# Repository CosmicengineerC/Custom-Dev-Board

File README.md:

# Custom-Dev-Board
A custom dev board designed by me to allow me to create intricate projects

A minimal, high-performance prototyping board based on the Raspberry Pi RP2040.

Core Specs
MCU: Dual ARM Cortex-M0+ (133 MHz, 264 KB SRAM).

Storage: 2 MB QSPI Flash.

I/O: 20-pin breakout (GPIO, ADC, UART, SPI, I2C).

Clock: 12 MHz Crystal.

Power: USB-C (5V) to 3.3V LDO.

## How to Use:
Honestly idk, however you want, its a cheaper version of an esp-32, meant for small projects, its meant to be disposable in the sense of messing it up before a 100 dollar chip.

## Why I made this:

I made this because i wanted to test my skills, and allow me to easily create more intricate projects with ease. It is also a good starter project to learn the intricacies of PCB design.

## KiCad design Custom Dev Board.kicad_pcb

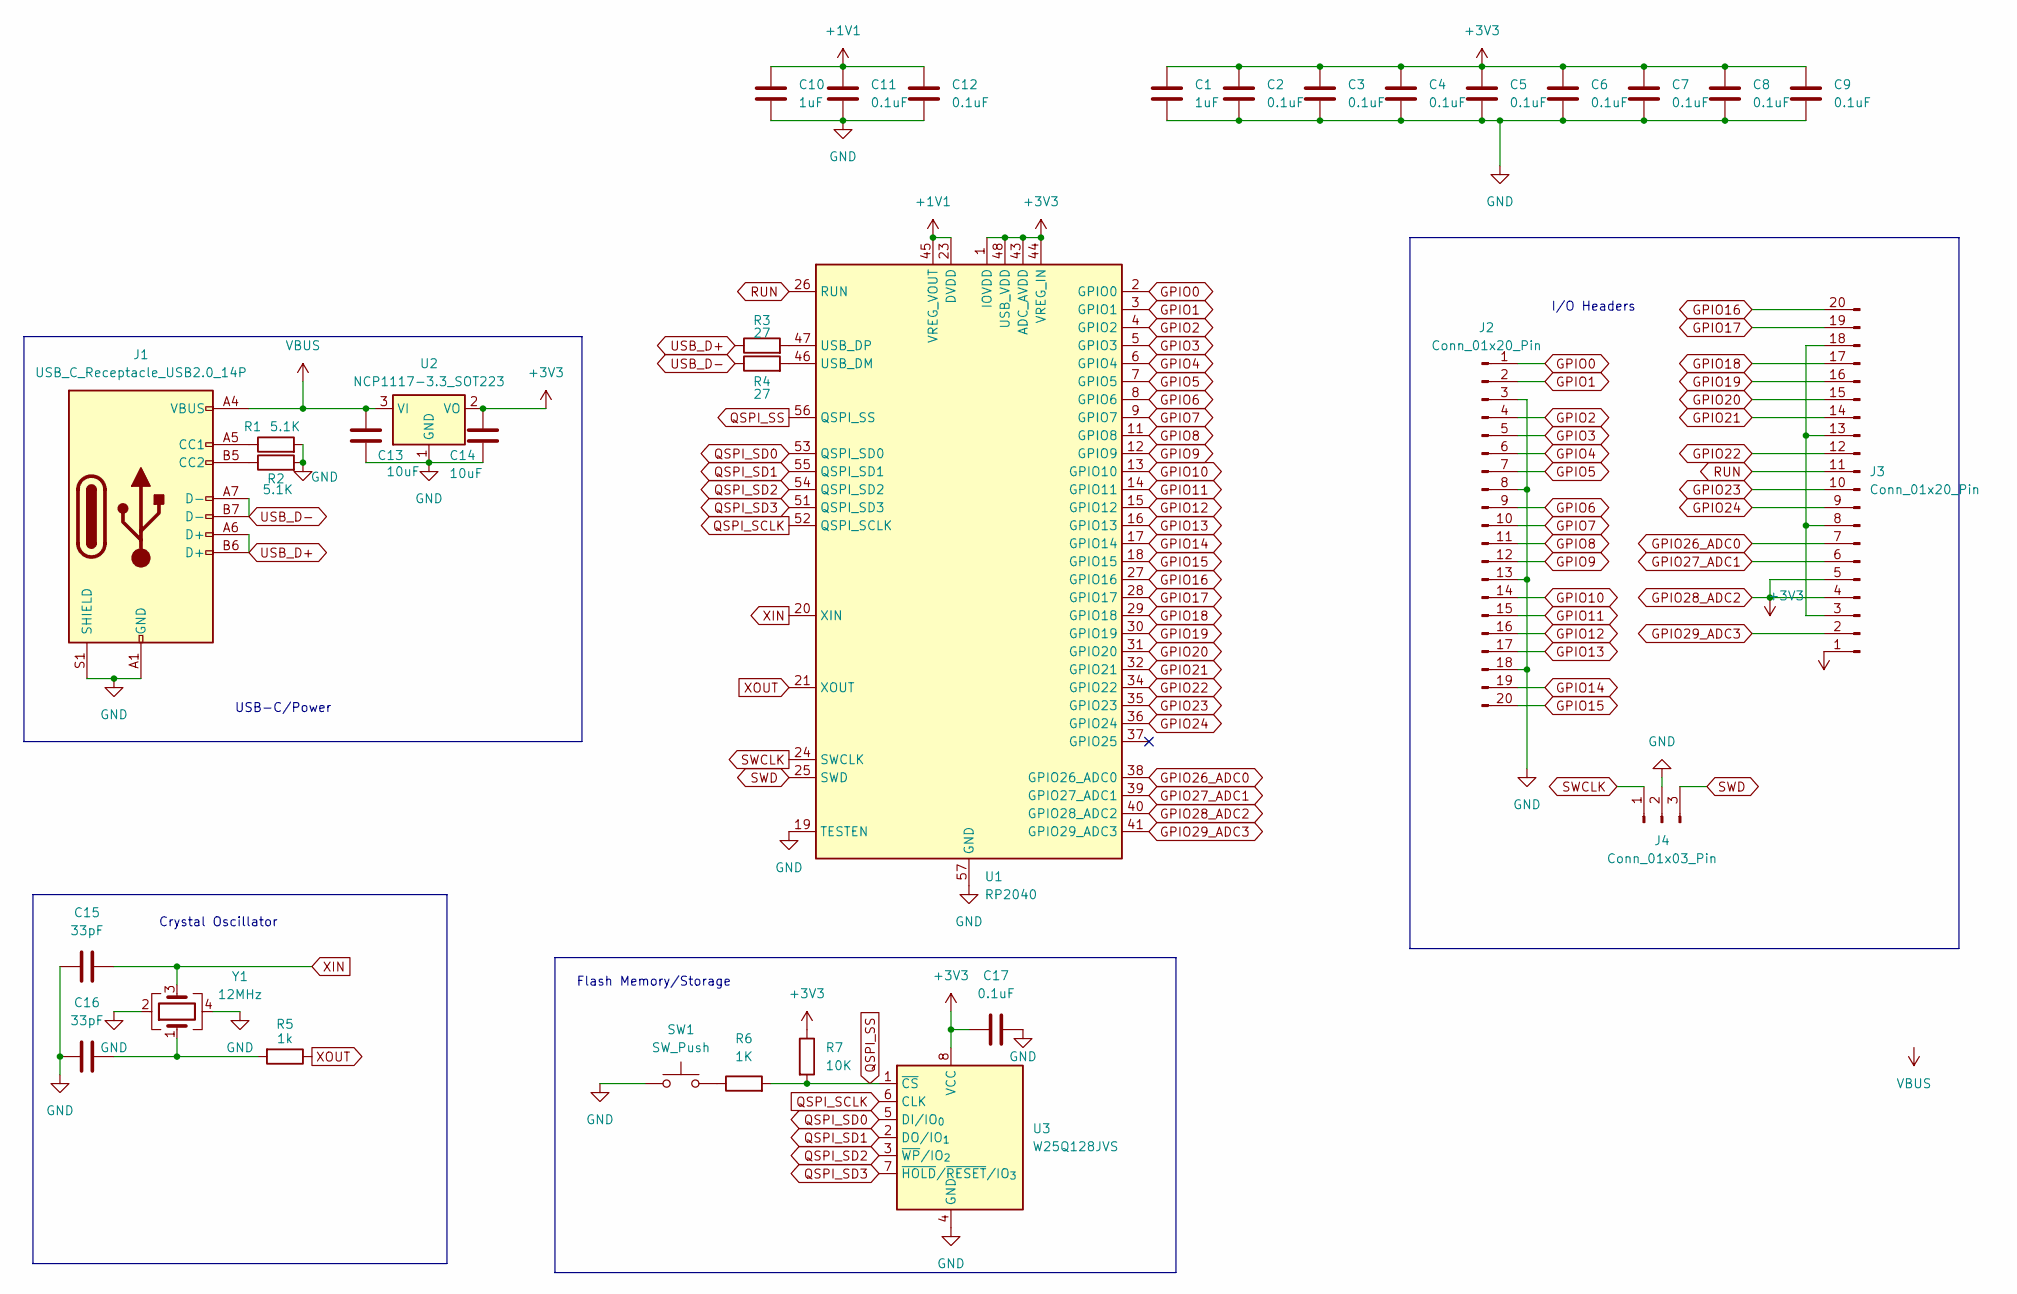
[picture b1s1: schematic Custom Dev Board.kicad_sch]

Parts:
C1, C10: 1uF; C_0402_1005Metric
C2, C3, C4, C5, C6, C7, C8, C9, C11, C12, C17: 0.1uF; C_0402_1005Metric
C13, C14: 10uF; C_0603_1608Metric
C15, C16: 33pF; C_0402_1005Metric
J1: USB_C_Receptacle_USB2.0_14P; USB_C_Receptacle_HRO_TYPE-C-31-M-12
J2, J3: Conn_01x20_Pin; PinHeader_1x20_P2.54mm_Vertical
J4: Conn_01x03_Pin; PinHeader_1x03_P2.54mm_Vertical
R1, R2: 5.1K; R_0402_1005Metric
R3, R4: 27; R_0402_1005Metric
R5: 1k; R_0402_1005Metric
R6: 1K; R_0402_1005Metric
R7: 10K; R_0402_1005Metric
SW1: SW_Push; SW_Push_SPST_NO_Alps_SKRK
U1: RP2040; QFN-56-1EP_7x7mm_P0.4mm_EP3.2x3.2mm
U2: NCP1117-3.3_SOT223; SOT-223-3_TabPin2
U3: W25Q128JVS; SOIC-8_5.3x5.3mm_P1.27mm
Y1: 12MHz; Crystal_SMD_3225-4Pin_3.2x2.5mm

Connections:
+1V1: C10.1, C11.1, C12.1, U1.23 (DVDD), U1.45 (VREG_VOUT), U1.50 (DVDD)
GND: C1.2, C2.2, C3.2, C4.2, C5.2, C6.2, C7.2, C8.2, C9.2, C10.2, C11.2, C12.2, C13.2, C14.2, C15.1, C16.1, C17.1, J1.A1 (GND), J1.A12 (GND), J1.B1 (GND), J1.B12 (GND), J1.S1 (SHIELD), J2.3, J2.8, J2.13, J2.18, J4.2, R1.2, R2.2, SW1.1, U1.19 (TESTEN), U1.57 (GND), U2.1 (GND), U3.4 (GND), Y1.2, Y1.4
GPIO0: J2.1, U1.2 (GPIO0)
GPIO1: J2.2, U1.3 (GPIO1)
GPIO2: J2.4, U1.4 (GPIO2)
GPIO3: J2.5, U1.5 (GPIO3)
GPIO4: J2.6, U1.6 (GPIO4)
GPIO5: J2.7, U1.7 (GPIO5)
GPIO6: J2.9, U1.8 (GPIO6)
GPIO7: J2.10, U1.9 (GPIO7)
GPIO8: J2.11, U1.11 (GPIO8)
GPIO9: J2.12, U1.12 (GPIO9)
GPIO10: J2.14, U1.13 (GPIO10)
GPIO11: J2.15, U1.14 (GPIO11)
GPIO12: J2.16, U1.15 (GPIO12)
GPIO13: J2.17, U1.16 (GPIO13)
GPIO14: J2.19, U1.17 (GPIO14)
GPIO15: J2.20, U1.18 (GPIO15)
GPIO16: J3.20, U1.27 (GPIO16)
GPIO17: J3.19, U1.28 (GPIO17)
GPIO18: J3.17, U1.29 (GPIO18)
GPIO19: J3.16, U1.30 (GPIO19)
GPIO20: J3.15, U1.31 (GPIO20)
GPIO21: J3.14, U1.32 (GPIO21)
GPIO22: J3.12, U1.34 (GPIO22)
GPIO23: J3.10, U1.35 (GPIO23)
GPIO24: J3.9, U1.36 (GPIO24)
GPIO26_ADC0: J3.7, U1.38 (GPIO26_ADC0)
GPIO27_ADC1: J3.6, U1.39 (GPIO27_ADC1)
GPIO28_ADC2: C1.1, C2.1, C3.1, C4.1, C5.1, C6.1, C7.1, C8.1, C9.1, C14.1, C17.2, J3.4, J3.5, R7.1, U1.1 (IOVDD), U1.10 (IOVDD), U1.22 (IOVDD), U1.33 (IOVDD), U1.40 (GPIO28_ADC2), U1.42 (IOVDD), U1.43 (ADC_AVDD), U1.44 (VREG_IN), U1.48 (USB_VDD), U1.49 (IOVDD), U2.2 (VO), U3.8 (VCC)
GPIO29_ADC3: J3.2, U1.41 (GPIO29_ADC3)
unnamed: C16.2, R5.2, Y1.1
unnamed: J1.A5 (CC1), R1.1
unnamed: J1.B5 (CC2), R2.1
unnamed: J3.3, J3.8, J3.13, J3.18
unnamed: R6.1, SW1.2
unnamed: R4.2, U1.46 (USB_DM)
unnamed: R3.2, U1.47 (USB_DP)
QSPI_SCLK: U1.52 (QSPI_SCLK), U3.6 (CLK)
QSPI_SD0: U1.53 (QSPI_SD0), U3.5 (DI/IO_{0})
QSPI_SD1: U1.55 (QSPI_SD1), U3.2 (DO/IO_{1})
QSPI_SD2: U1.54 (QSPI_SD2), U3.3 (~WP/IO_{2})
QSPI_SD3: U1.51 (QSPI_SD3), U3.7 (~HOLD/~RESET/IO_{3})
QSPI_SS: R6.2, R7.2, U1.56 (QSPI_SS), U3.1 (~CS)
RUN: J3.11, U1.26 (RUN)
SWCLK: J4.1, U1.24 (SWCLK)
SWD: J4.3, U1.25 (SWD)
USB_D+: J1.A6 (D+), J1.B6 (D+), R3.1
USB_D-: J1.A7 (D-), J1.B7 (D-), R4.1
VBUS: C13.1, J1.A4 (VBUS), J1.A9 (VBUS), J1.B4 (VBUS), J1.B9 (VBUS), J3.1, U2.3 (VI)
XIN: C15.2, U1.20 (XIN), Y1.3
XOUT: R5.1, U1.21 (XOUT)

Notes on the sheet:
Crystal Oscillator
I/O Headers
Flash Memory/Storage
USB-C/Power

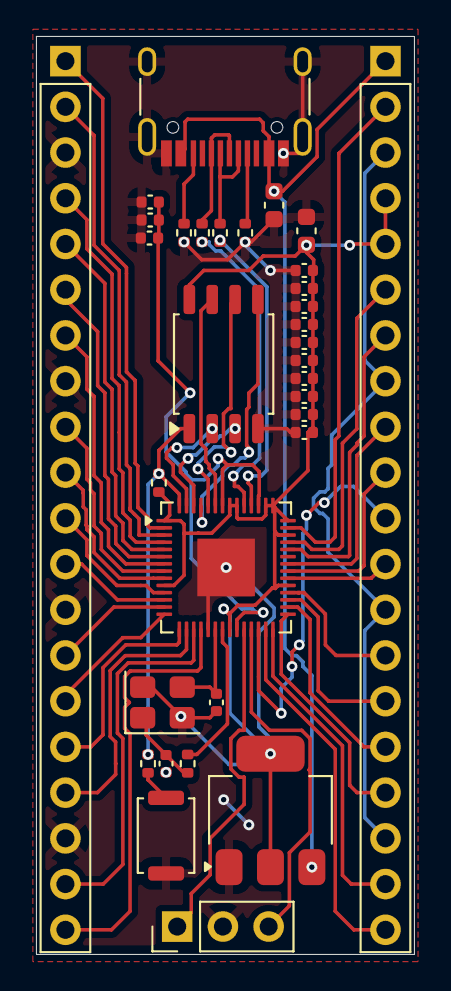
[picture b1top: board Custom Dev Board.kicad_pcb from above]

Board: 2 copper layers, 21.0 x 51.0 mm, 33 parts (0 on the bottom side), 52 nets.

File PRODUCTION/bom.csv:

Designator,Footprint,Quantity,Value,LCSC Part #
"C1, C10",0402,2,1uF,
"C11, C12, C17, C2, C3, C4, C5, C6, C7, C8, C9",0402,11,0.1uF,
"C13, C14",0603,2,10uF,
"C15, C16",0402,2,33pF,
J1,USB_C_Receptacle_HRO_TYPE-C-31-M-12,1,USB_C_Receptacle_USB2.0_14P,
"J2, J3",PinHeader_1x20_P2.54mm_Vertical,2,Conn_01x20_Pin,
J4,PinHeader_1x03_P2.54mm_Vertical,1,Conn_01x03_Pin,
"R1, R2",0402,2,5.1K,
"R3, R4",0402,2,27,
"R5, R6",0402,2,1k,
R7,0402,1,10K,
SW1,SW_Push_SPST_NO_Alps_SKRK,1,SW_Push,
U1,QFN-56-1EP_7x7mm_P0.4mm_EP3.2x3.2mm,1,RP2040,
U2,SOT-223-3_TabPin2,1,NCP1117-3.3_SOT223,
U3,SOIC-8_5.3x5.3mm_P1.27mm,1,W25Q128JVS,
Y1,Crystal_SMD_3225-4Pin_3.2x2.5mm,1,12MHz,

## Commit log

2026-04-27 Extract test2.zip and organize production files
    Agent-Logs-Url: https://github.com/CosmicengineerC/Custom-Dev-Board/sessions/21f49409-3f64-4ffb-bc69-82f0bee15f04
2026-04-27 Organize PRODUCTION files into subdirectories by type
    Agent-Logs-Url: https://github.com/CosmicengineerC/Custom-Dev-Board/sessions/21f49409-3f64-4ffb-bc69-82f0bee15f04
2026-04-27 Update README with core specs for dev board
    Added core specifications for the custom dev board.
2026-05-12 Update README with usage and project motivation
    Added usage instructions and motivation for the project.
2026-05-15 Add contents from NEW production.zip into PRODUCTION
    Agent-Logs-Url: https://github.com/CosmicengineerC/Custom-Dev-Board/sessions/8466e7df-6ea2-407b-8489-151740f0e4d2
